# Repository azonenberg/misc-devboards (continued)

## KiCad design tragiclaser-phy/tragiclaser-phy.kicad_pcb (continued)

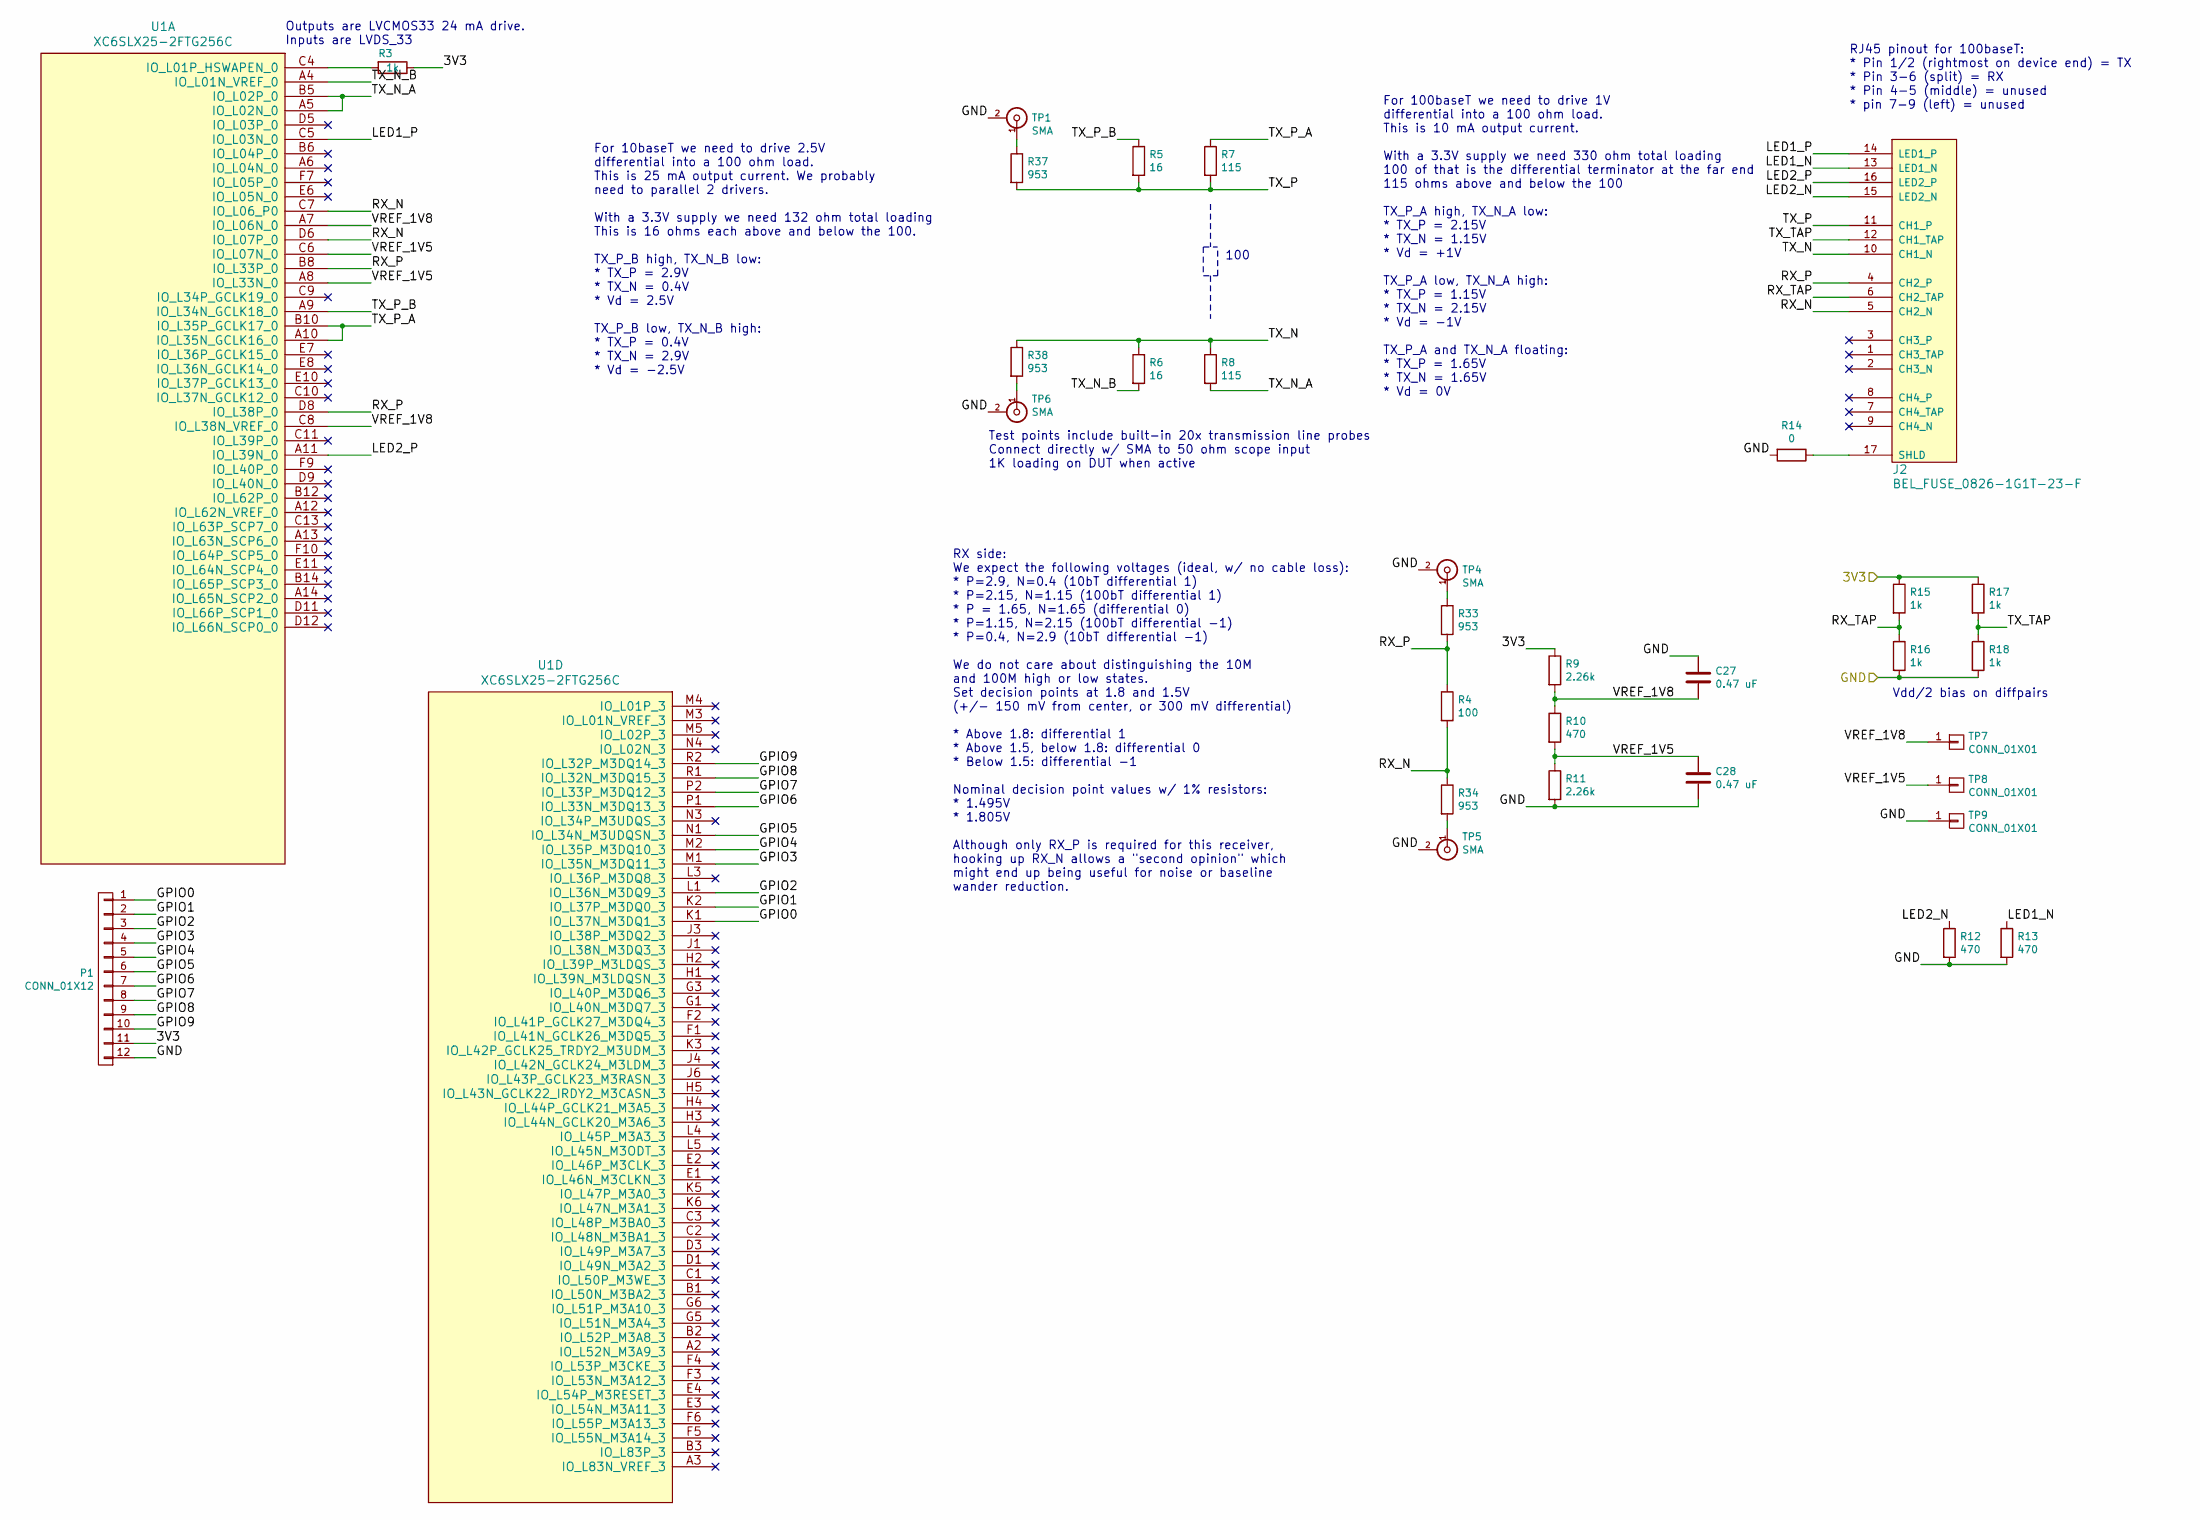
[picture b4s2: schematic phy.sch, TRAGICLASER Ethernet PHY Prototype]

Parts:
C27, C28: 0.47 uF; EIA_0402_CAP_NOSILK
J2: BEL_FUSE_0826-1G1T-23-F; CONN_BELFUSE_0826_1G1T_23_F
P1: CONN_01X12; CONN_HEADER_2.54MM_2x6_RA
R3, R15, R16, R17, R18: 1k; EIA_0402_RES_NOSILK
R4: 100; EIA_0402_RES_NOSILK
R5, R6: 16; EIA_0402_RES_NOSILK
R7, R8: 115; EIA_0402_RES_NOSILK
R9, R11: 2.26k; EIA_0402_RES_NOSILK
R10, R12, R13: 470; EIA_0402_RES_NOSILK
R14: 0; EIA_0402_RES_NOSILK
R33, R34, R37, R38: 953; EIA_0402_RES_NOSILK
TP1, TP4, TP5, TP6: SMA; CONN_SMA_EDGE_SAMTEC_SMA_J_P_H_ST_EM1
TP7, TP8: CONN_01X01; TESTPOINT_SMT_0.5MM
TP9: CONN_01X01; TESTPOINT_SMT_KEYSTONE_5016
U1: XC6SLX25-2FTG256C; BGA_256_17x17_FULLARRAY_1MM

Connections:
/3V3: P1.11, R3.1, R9.1, R15.1, R17.1; also elsewhere on the board
/GND: C27.1, C28.2, P1.12, R11.2, R12.2, R13.2, R14.2, R16.2, R18.2, TP1.2 (Ext), TP4.2 (Ext), TP5.2 (Ext), TP6.2 (Ext), TP9.1; also elsewhere on the board
/PHY/GPIO0: P1.1, U1.K1 (IO_L37N_M3DQ1_3)
/PHY/GPIO1: P1.2, U1.K2 (IO_L37P_M3DQ0_3)
/PHY/GPIO2: P1.3, U1.L1 (IO_L36N_M3DQ9_3)
/PHY/GPIO3: P1.4, U1.M1 (IO_L35N_M3DQ11_3)
/PHY/GPIO4: P1.5, U1.M2 (IO_L35P_M3DQ10_3)
/PHY/GPIO5: P1.6, U1.N1 (IO_L34N_M3UDQSN_3)
/PHY/GPIO6: P1.7, U1.P1 (IO_L33N_M3DQ13_3)
/PHY/GPIO7: P1.8, U1.P2 (IO_L33P_M3DQ12_3)
/PHY/GPIO8: P1.9, U1.R1 (IO_L32N_M3DQ15_3)
/PHY/GPIO9: P1.10, U1.R2 (IO_L32P_M3DQ14_3)
/PHY/LED1_N: J2.13 (LED1_N), R13.1
/PHY/LED1_P: J2.14 (LED1_P), U1.C5 (IO_L03N_0)
/PHY/LED2_N: J2.15 (LED2_N), R12.1
/PHY/LED2_P: J2.16 (LED2_P), U1.A11 (IO_L39N_0)
/PHY/RX_N: J2.5 (CH2_N), R4.2, R34.1, U1.C7 (IO_L06_P0), U1.D6 (IO_L07P_0)
/PHY/RX_P: J2.4 (CH2_P), R4.1, R33.2, U1.B8 (IO_L33P_0), U1.D8 (IO_L38P_0)
/PHY/RX_TAP: J2.6 (CH2_TAP), R15.2, R16.1
/PHY/TX_N: J2.10 (CH1_N), R6.1, R8.1, R38.1
/PHY/TX_N_A: R8.2, U1.A5 (IO_L02N_0), U1.B5 (IO_L02P_0)
/PHY/TX_N_B: R6.2, U1.A4 (IO_L01N_VREF_0)
/PHY/TX_P: J2.11 (CH1_P), R5.2, R7.2, R37.2
/PHY/TX_P_A: R7.1, U1.A10 (IO_L35N_GCLK16_0), U1.B10 (IO_L35P_GCLK17_0)
/PHY/TX_P_B: R5.1, U1.A9 (IO_L34N_GCLK18_0)
/PHY/TX_TAP: J2.12 (CH1_TAP), R17.2, R18.1
/PHY/VREF_1V5: C28.1, R10.2, R11.1, TP8.1, U1.A8 (IO_L33N_0), U1.C6 (IO_L07N_0)
/PHY/VREF_1V8: C27.2, R9.2, R10.1, TP7.1, U1.A7 (IO_L06N_0), U1.C8 (IO_L38N_VREF_0)
unnamed: J2.17 (SHLD), R14.1
unnamed: R3.2, U1.C4 (IO_L01P_HSWAPEN_0)
unnamed: R33.1, TP4.1 (In)
unnamed: R34.2, TP5.1 (In)
unnamed: R37.1, TP1.1 (In)
unnamed: R38.2, TP6.1 (In)

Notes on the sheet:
RJ45 pinout for 100baseT: * Pin 1/2 (rightmost on device end) = TX * Pin 3-6 (split) = RX * Pin 4-5 (middle) = unused * pin 7-9 (left) = unused
For 10baseT we need to drive 2.5V differential into a 100 ohm load. This is 25 mA output current. We probably need to parallel 2 drivers. With a 3.3V supply we need 132 ohm total loading This is 16 ohms each above and below the 100. TX_P_B high, TX_N_B low: * TX_P = 2.9V * TX_N = 0.4V * Vd = 2.5V T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
For 100baseT we need to drive 1V differential into a 100 ohm load. This is 10 mA output current. With a 3.3V supply we need 330 ohm total loading 100 of that is the differential terminator at the far end 115 ohms above and below the 100 TX_P_A high, TX_N_A low: * TX_P = 2.15V * TX_N = 1.15V * Vd = 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
100
Vdd/2 bias on diffpairs
RX side: We expect the following voltages (ideal, w/ no cable loss): * P=2.9, N=0.4 (10bT differential 1) * P=2.15, N=1.15 (100bT differential 1) * P = 1.65, N=1.65 (differential 0) * P=1.15, N=2.15 (100bT differential -1) * P=0.4, N=2.9 (10bT differential -1) We do not care about distinguishing th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
Outputs are LVCMOS33 24 mA drive. Inputs are LVDS_33
Test points include built-in 20x transmission line probes Connect directly w/ SMA to 50 ohm scope input 1K loading on DUT when active

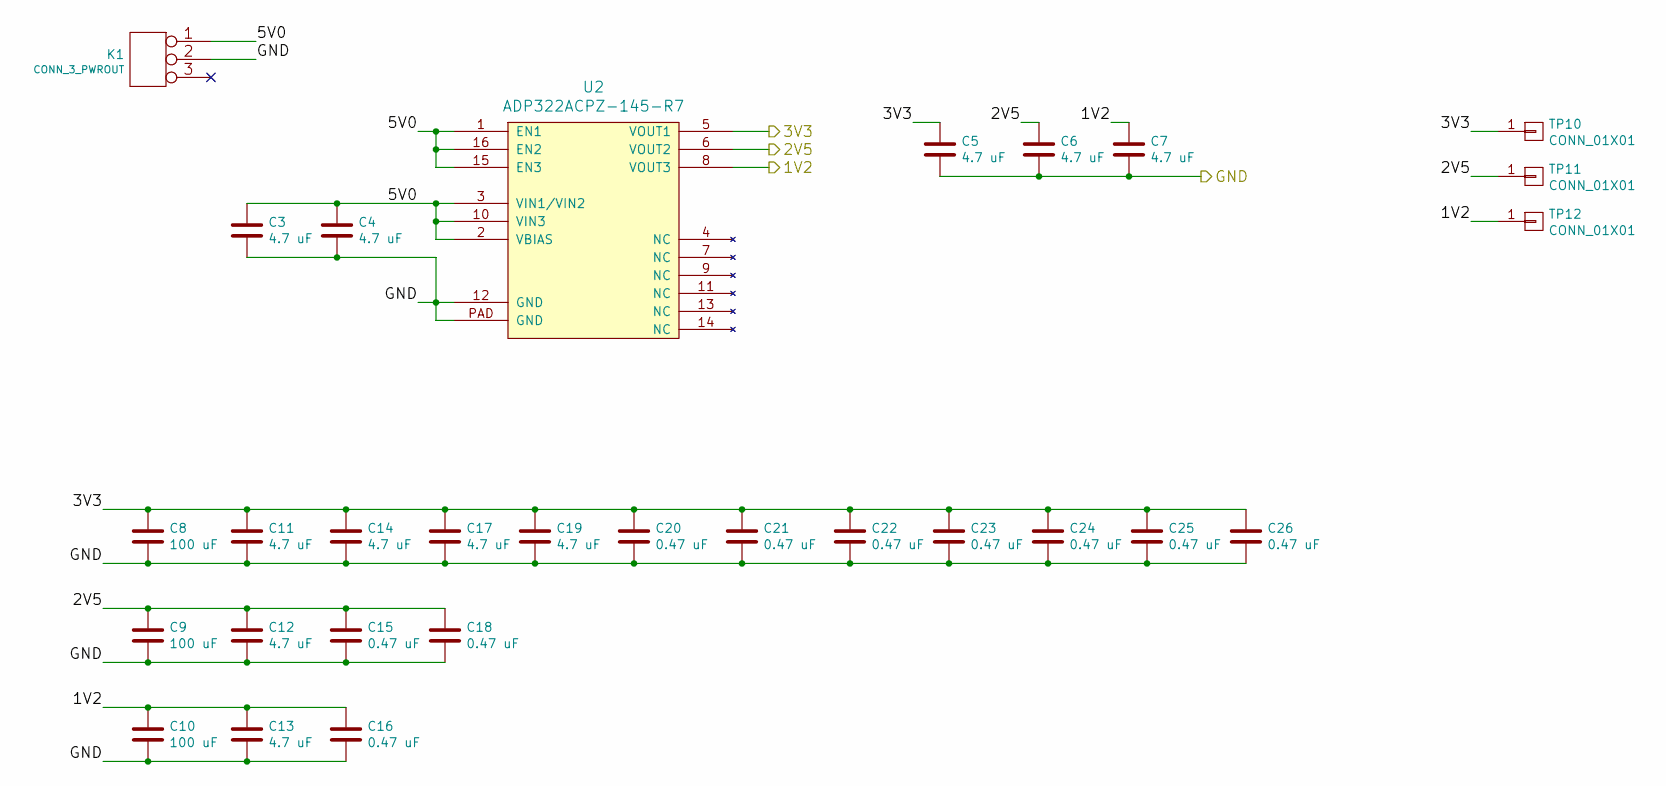
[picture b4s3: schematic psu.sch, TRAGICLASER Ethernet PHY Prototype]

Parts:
C3, C4, C5, C6, C7, C11, C12, C13, C14, C17, C19: 4.7 uF; EIA_0603_CAP_NOSILK
C8, C9, C10: 100 uF; EIA_1206_CAP_NOSILK
C15, C16, C18, C20, C21, C22, C23, C24, C25, C26: 0.47 uF; EIA_0402_CAP_NOSILK
K1: CONN_3_PWROUT; CONN_CUI_PJ-058BH_HIPWR_BARREL_NOSLOT
TP10, TP11, TP12: CONN_01X01; TESTPOINT_SMT_0.5MM
U2: ADP322ACPZ-145-R7; QFN_16_0.5MM_3x3MM

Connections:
/1V2: C7.1, C10.1, C13.1, C16.1, TP12.1, U2.8 (VOUT3); also elsewhere on the board
/2V5: C6.1, C9.1, C12.1, C15.1, C18.1, TP11.1, U2.6 (VOUT2); also elsewhere on the board
/3V3: C5.1, C8.1, C11.1, C14.1, C17.1, C19.1, C20.1, C21.1, C22.1, C23.1, C24.1, C25.1, C26.1, TP10.1, U2.5 (VOUT1); also elsewhere on the board
/GND: C3.2, C4.2, C5.2, C6.2, C7.2, C8.2, C9.2, C10.2, C11.2, C12.2, C13.2, C14.2, C15.2, C16.2, C17.2, C18.2, C19.2, C20.2, C21.2, C22.2, C23.2, C24.2, C25.2, C26.2, K1.2 (PM), U2.12 (GND), U2.PAD (GND); also elsewhere on the board
/Power Supply/5V0: C3.1, C4.1, K1.1, U2.1 (EN1), U2.2 (VBIAS), U2.3 (VIN1/VIN2), U2.10 (VIN3), U2.15 (EN3), U2.16 (EN2)

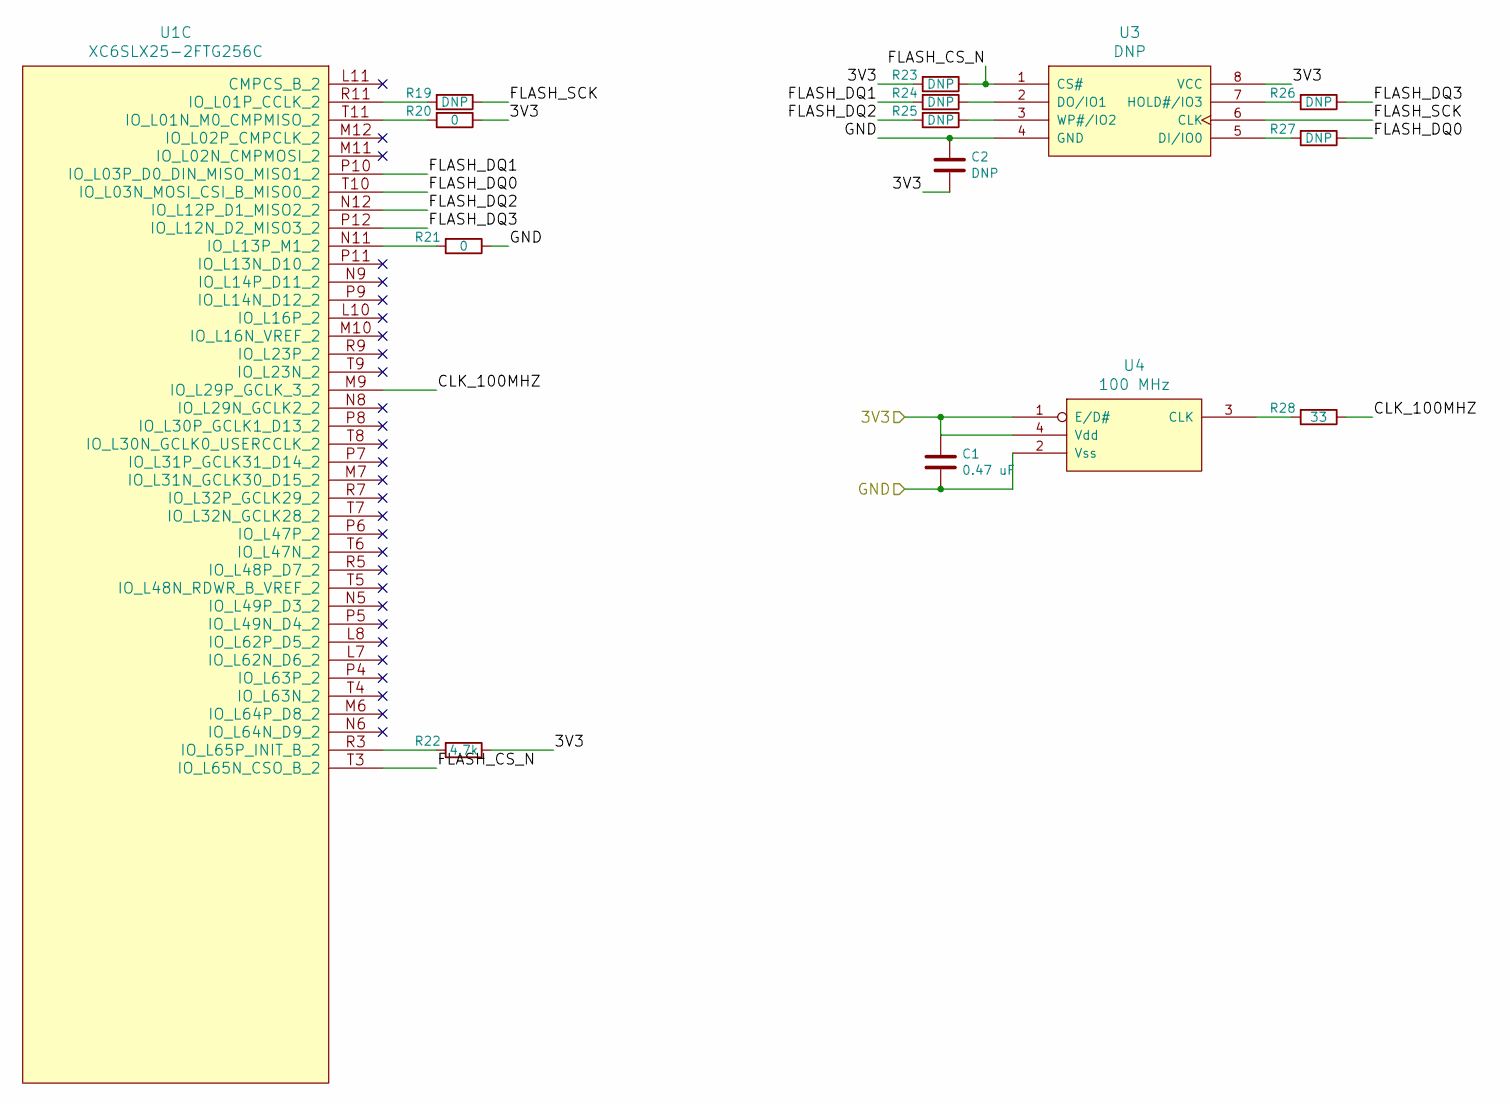
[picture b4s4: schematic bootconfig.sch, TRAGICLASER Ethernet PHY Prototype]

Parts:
C1: 0.47 uF; EIA_0402_CAP_NOSILK
C2: DNP; EIA_0402_CAP_NOSILK
R19, R23, R24, R25, R26, R27: DNP; EIA_0402_RES_NOSILK
R20, R21: 0; EIA_0402_RES_NOSILK
R22: 4.7k; EIA_0402_RES_NOSILK
R28: 33; EIA_0402_RES_NOSILK
U1: XC6SLX25-2FTG256C; BGA_256_17x17_FULLARRAY_1MM
U3: DNP; SOIC_8_3.9MM
U4: 100 MHz; OSCILLATOR_3.2x2.5

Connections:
/3V3: C1.1, C2.2, R20.1, R22.1, R23.2, U3.8 (VCC), U4.1 (E/D#), U4.4 (Vdd); also elsewhere on the board
/Boot/Config/CLK_100MHZ: R28.1, U1.M9 (IO_L29P_GCLK_3_2)
/Boot/Config/FLASH_CS_N: R23.1, U1.T3 (IO_L65N_CSO_B_2), U3.1 (CS#)
/Boot/Config/FLASH_DQ0: R27.1, U1.T10 (IO_L03N_MOSI_CSI_B_MISO0_2)
/Boot/Config/FLASH_DQ1: R24.2, U1.P10 (IO_L03P_D0_DIN_MISO_MISO1_2)
/Boot/Config/FLASH_DQ2: R25.2, U1.N12 (IO_L12P_D1_MISO2_2)
/Boot/Config/FLASH_DQ3: R26.1, U1.P12 (IO_L12N_D2_MISO3_2)
/Boot/Config/FLASH_SCK: R19.1, U3.6 (CLK)
/GND: C1.2, C2.1, R21.1, U3.4 (GND), U4.2 (Vss); also elsewhere on the board
unnamed: R19.2, U1.R11 (IO_L01P_CCLK_2)
unnamed: R20.2, U1.T11 (IO_L01N_M0_CMPMISO_2)
unnamed: R21.2, U1.N11 (IO_L13P_M1_2)
unnamed: R22.2, U1.R3 (IO_L65P_INIT_B_2)
unnamed: R24.1, U3.2 (DO/IO1)
unnamed: R25.1, U3.3 (WP#/IO2)
unnamed: R26.2, U3.7 (HOLD#/IO3)
unnamed: R27.2, U3.5 (DI/IO0)
unnamed: R28.2, U4.3 (CLK)

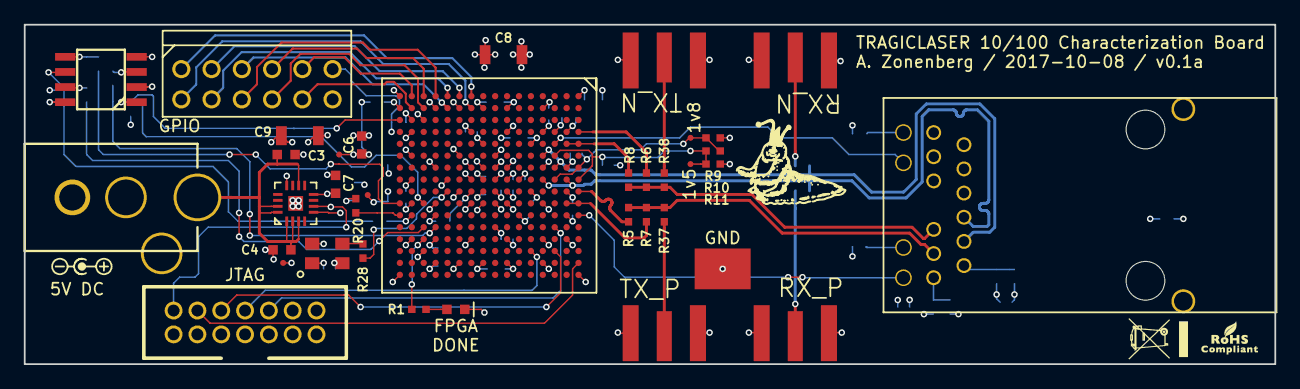
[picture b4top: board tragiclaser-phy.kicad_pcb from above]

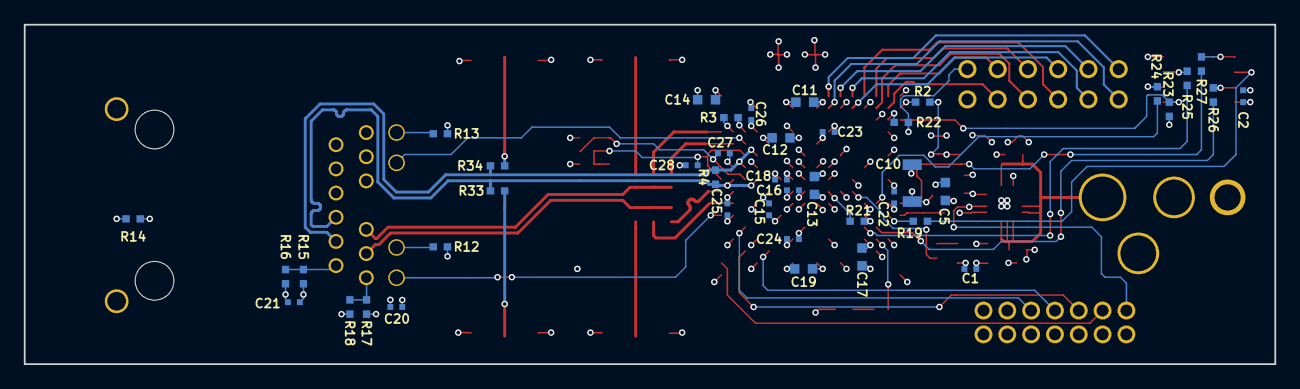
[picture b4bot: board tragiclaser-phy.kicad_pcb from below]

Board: 4 copper layers, 105.0 x 28.5 mm, 79 parts (42 on the bottom side), 60 nets.
